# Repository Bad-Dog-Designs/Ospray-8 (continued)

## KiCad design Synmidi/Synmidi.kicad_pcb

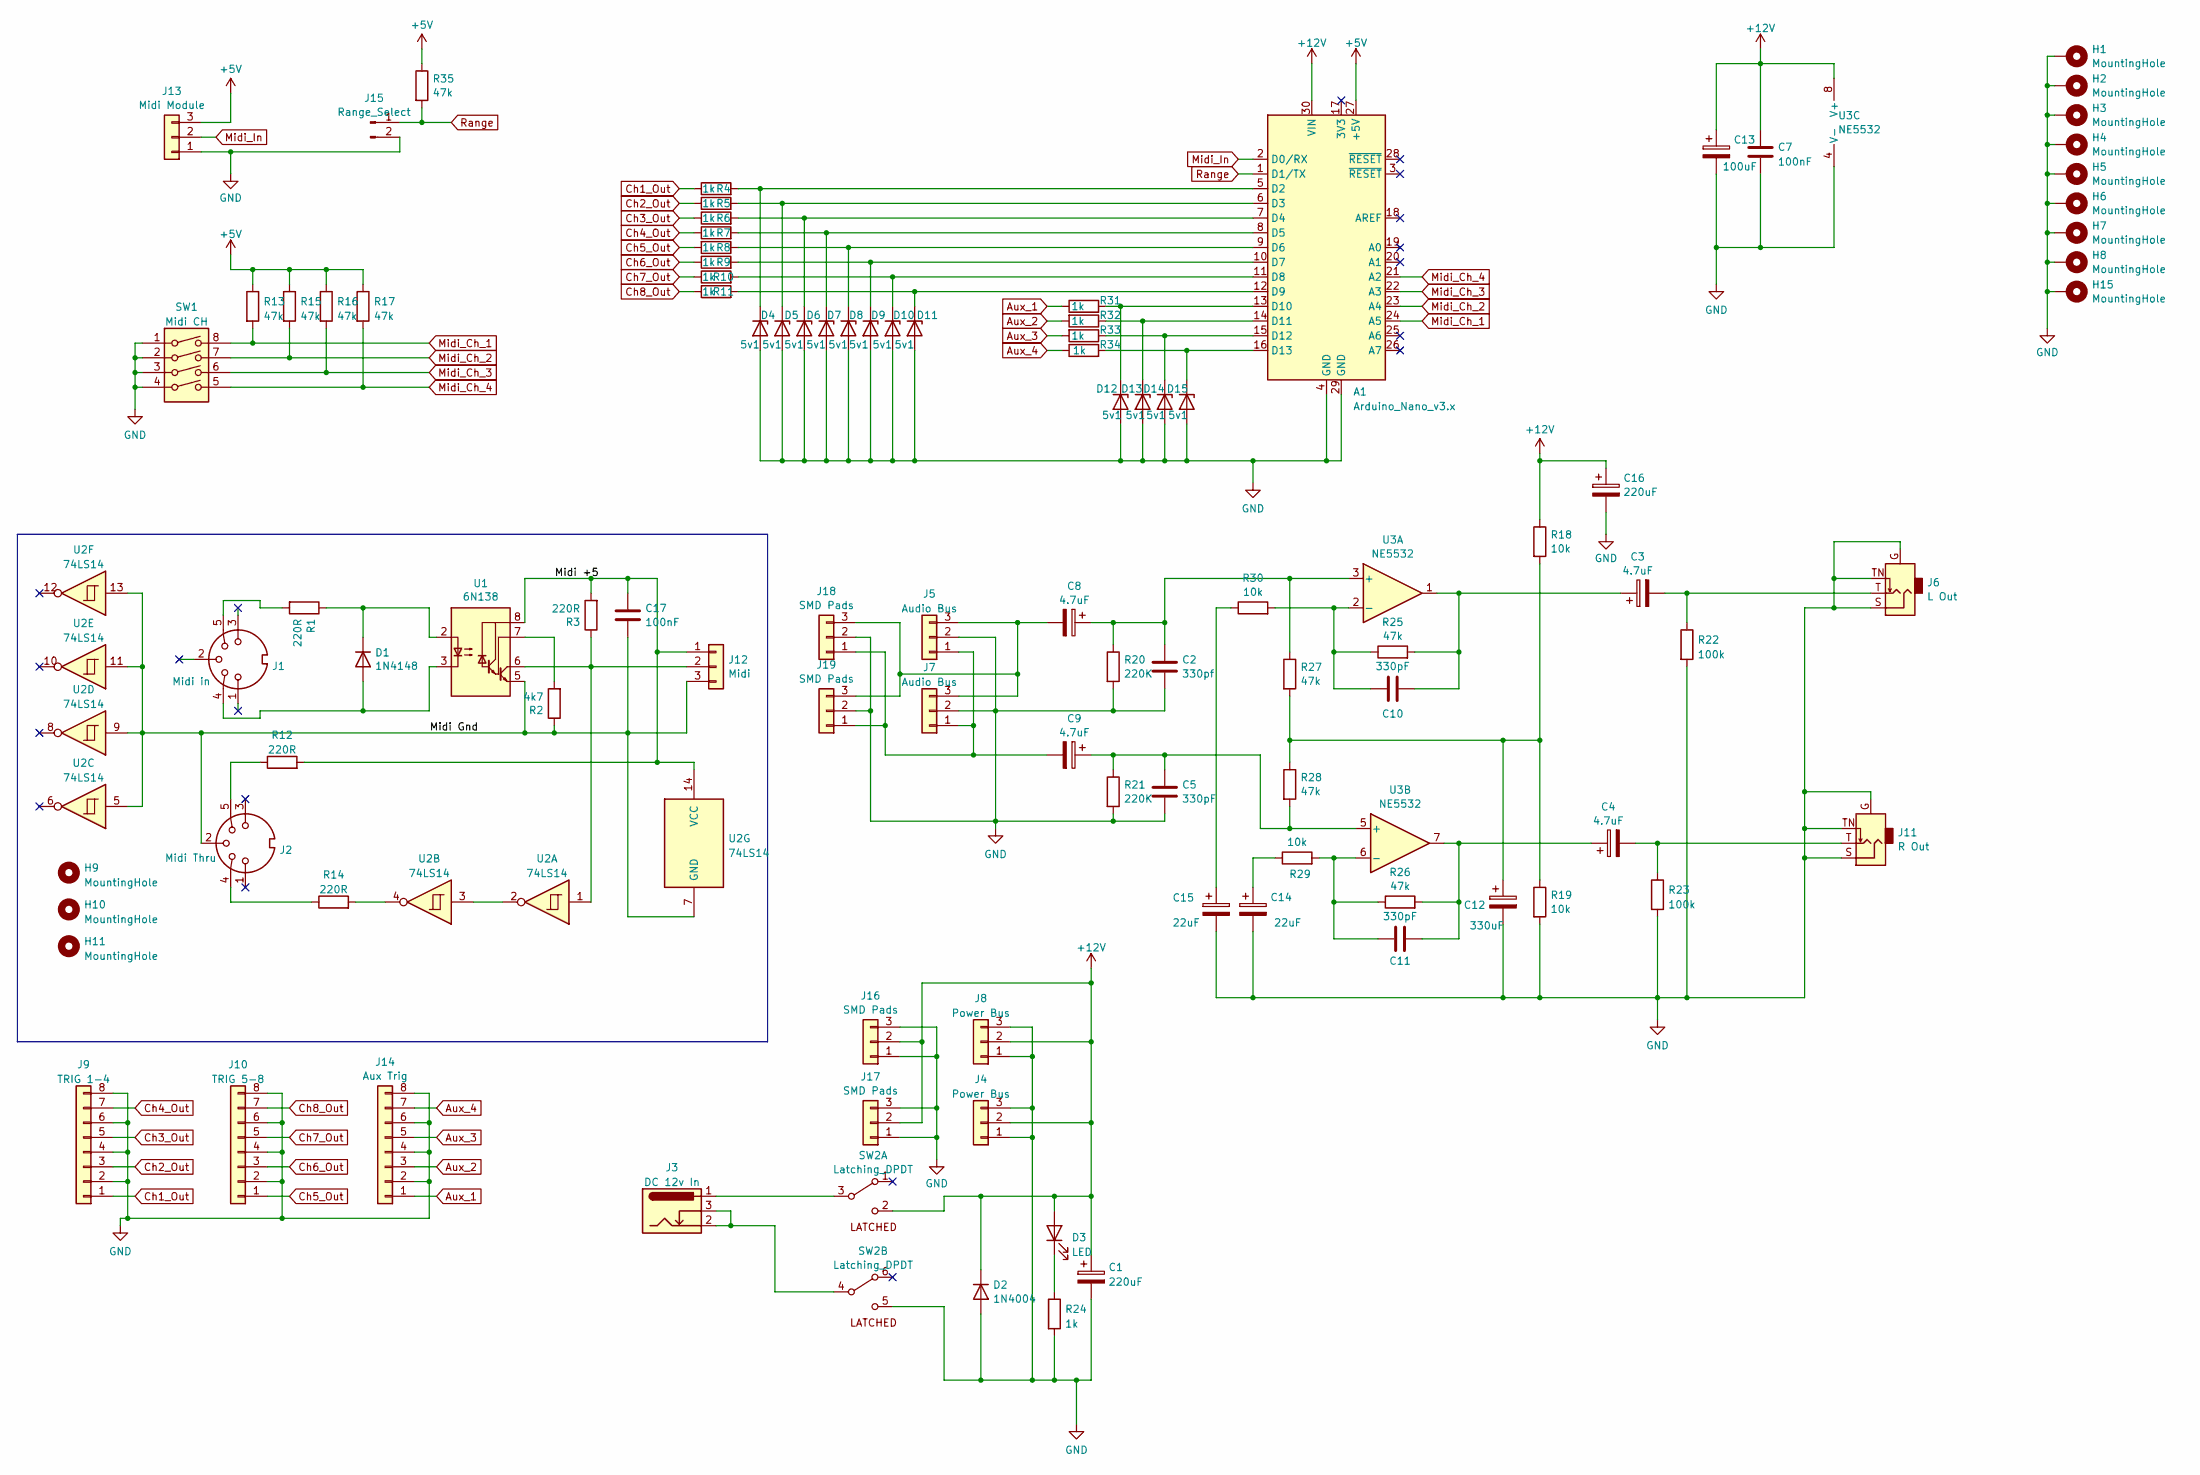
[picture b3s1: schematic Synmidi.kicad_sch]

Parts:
A1: Arduino_Nano_v3.x; Arduino_Nano
C1, C16: 220uF; CP_Radial_D10.0mm_P5.00mm
C2: 330pf; C_Disc_D4.3mm_W1.9mm_P5.00mm
C3, C4, C8, C9: 4.7uF; CP_Radial_D4.0mm_P1.50mm
C5, C10, C11: 330pF; C_Disc_D4.3mm_W1.9mm_P5.00mm
C7, C17: 100nF; C_0805_2012Metric
C12: 330uF; CP_Radial_D10.0mm_P5.00mm
C13: 100uF; CP_Radial_D8.0mm_P3.50mm
C14, C15: 22uF; CP_Radial_D5.0mm_P2.00mm
D1: 1N4148; D_MELF
D2: 1N4004; D_DO-41_SOD81_P10.16mm_Horizontal
D3: LED; LED_D3.0mm_FlatTop
D4, D5, D6, D7, D8, D9, D10, D11, D12, D13, D14, D15: 5v1; D_SOD-323
H1, H2, H3, H4, H5, H6, H7, H8, H9, H10, H11, H15: MountingHole; MountingHole_3.2mm_M3_DIN965_Pad
J1: Midi in; Midi_Socket
J2: Midi Thru; Midi_Socket
J3: DC 12v In; BarrelJack_GCT_DCJ200-10-A_Horizontal
J4, J8: Power Bus; PinHeader_1x03_P2.54mm_Horizontal
J5, J7: Audio Bus; PinHeader_1x03_P2.54mm_Horizontal
J6: L Out; 6.35mm_Socket_Mono
J9: TRIG 1-4; JST_EH_S8B-EH_1x08_P2.50mm_Horizontal
J10: TRIG 5-8; JST_EH_S8B-EH_1x08_P2.50mm_Horizontal
J11: R Out; 6.35mm_Socket_Mono
J12: Midi; PinHeader_1x03_P2.54mm_Vertical
J13: Midi Module; PinHeader_1x03_P2.54mm_Vertical
J14: Aux Trig; JST_EH_S8B-EH_1x08_P2.50mm_Horizontal
J15: Range_Select; PinHeader_1x02_P2.54mm_Vertical
J16, J17, J18, J19: SMD Pads; Bus Connector
R1, R3, R12, R14: 220R; R_1206_3216Metric
R2: 4k7; R_1206_3216Metric
R4, R5, R6, R7, R8, R9, R10, R11, R24, R31, R32, R33, R34: 1k; R_1206_3216Metric
R13, R15, R16, R17, R25, R26, R27, R28, R35: 47k; R_1206_3216Metric
R18, R19, R29, R30: 10k; R_1206_3216Metric
R20, R21: 220K; R_1206_3216Metric
R22, R23: 100k; R_1206_3216Metric
SW1: Midi CH; SW_DIP_SPSTx04_Piano_CTS_Series194-4MSTN_W7.62mm_P2.54mm
SW2: Latching_DPDT
U1: 6N138; DIP-8_W8.89mm_SMDSocket_LongPads
U2: 74LS14; SO-14_3.9x8.65mm_P1.27mm
U3: NE5532; SOIC-8_3.9x4.9mm_P1.27mm

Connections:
+5V: A1.27 (+5V), J13.3, R13.1, R15.1, R16.1, R17.1, R35.1
+12V: A1.30 (VIN), C1.1, C7.1, C13.1, C16.1, D2.1 (K), D3.2 (A), J4.2, J8.2, J16.2, J17.2, R18.1, SW2.2 (B), U3.8 (V+)
/Midi +5: C17.1, J12.1, R3.2, R12.2, U1.8 (VCC), U2.14 (VCC)
/Midi Gnd: C17.2, J2.2, J12.3, R2.1, U1.5 (GND), U2.5, U2.7 (GND), U2.9, U2.11, U2.13
Aux_1: J14.1, R31.1
Aux_2: J14.3, R32.2
Aux_3: J14.5, R33.2
Aux_4: J14.7, R34.1
Ch1_Out: J9.1, R4.1
Ch2_Out: J9.3, R5.1
Ch3_Out: J9.5, R6.1
Ch4_Out: J9.7, R7.1
Ch5_Out: J10.1, R8.2
Ch6_Out: J10.3, R9.1
Ch7_Out: J10.5, R10.1
Ch8_Out: J10.7, R11.1
GND: A1.4 (GND), A1.29 (GND), C1.2, C2.2, C5.2, C7.2, C12.2, C13.2, C14.2, C15.2, C16.2, D2.2 (A), D4.2 (A), D5.2 (A), D6.2 (A), D7.2 (A), D8.2 (A), D9.2 (A), D10.2 (A), D11.2 (A), D12.2 (A), D13.2 (A), D14.2 (A), D15.2 (A), H1.1, H2.1, H3.1, H4.1, H5.1, H6.1, H7.1, H8.1, H15.1, J4.1, J4.3, J5.2, J6.G, J6.S, J6.TN, J7.2, J8.1, J8.3, J9.2, J9.4, J9.6, J9.8, J10.2, J10.4, J10.6, J10.8, J11.G, J11.S, J11.TN, J13.1, J14.2, J14.4, J14.6, J14.8, J15.2, J16.1, J16.3, J17.1, J17.3, J18.2, J19.2, R19.2, R20.2, R21.2, R22.2, R23.2, R24.2, SW1.1, SW1.2, SW1.3, SW1.4, SW2.5 (B), U3.4 (V-)
Midi_Ch_1: A1.24 (A5), R13.2, SW1.8
Midi_Ch_2: A1.23 (A4), R15.2, SW1.7
Midi_Ch_3: A1.22 (A3), R16.2, SW1.6
Midi_Ch_4: A1.21 (A2), R17.2, SW1.5
Midi_In: A1.2 (D0/RX), J13.2
unnamed: A1.5 (D2), D4.1 (K), R4.2
unnamed: A1.6 (D3), D5.1 (K), R5.2
unnamed: A1.7 (D4), D6.1 (K), R6.2
unnamed: A1.8 (D5), D7.1 (K), R7.2
unnamed: A1.9 (D6), D8.1 (K), R8.1
unnamed: A1.10 (D7), D9.1 (K), R9.2
unnamed: A1.11 (D8), D10.1 (K), R10.2
unnamed: A1.12 (D9), D11.1 (K), R11.2
unnamed: A1.13 (D10), D12.1 (K), R31.2
unnamed: A1.14 (D11), D13.1 (K), R32.1
unnamed: A1.15 (D12), D14.1 (K), R33.1
unnamed: A1.16 (D13), D15.1 (K), R34.2
unnamed: C3.2, J6.T, R22.1
unnamed: C4.2, J11.T, R23.1
unnamed: C3.1, C10.2, R25.2, U3.1
unnamed: C4.1, C11.2, R26.2, U3.7
unnamed: C12.1, R18.2, R19.1, R27.2, R28.1
unnamed: C14.1, R29.1
unnamed: C15.1, R30.1
unnamed: D1.2 (A), J1.4, U1.3 (C2)
unnamed: D1.1 (K), R1.1, U1.2 (C1)
unnamed: D3.1 (K), R24.1
unnamed: J1.5, R1.2
unnamed: J2.4, R14.1
unnamed: J2.5, R12.1
unnamed: J12.2, R3.1, U1.6 (VO2), U2.1
unnamed: C9.2, J5.1, J7.1, J18.1, J19.1
unnamed: C8.2, J5.3, J7.3, J18.3, J19.3
unnamed: R14.2, U2.4
unnamed: J3.1, SW2.3 (C)
unnamed: J3.2, J3.3, SW2.4 (A)
unnamed: R2.2, U1.7 (VO1)
unnamed: U2.2, U2.3
unnamed: C2.1, C8.1, R20.1, R27.1, U3.3 (+)
unnamed: C10.1, R25.1, R30.2, U3.2 (-)
unnamed: C5.1, C9.1, R21.1, R28.2, U3.5 (+)
unnamed: C11.1, R26.1, R29.2, U3.6 (-)
Range: A1.1 (D1/TX), J15.1, R35.2

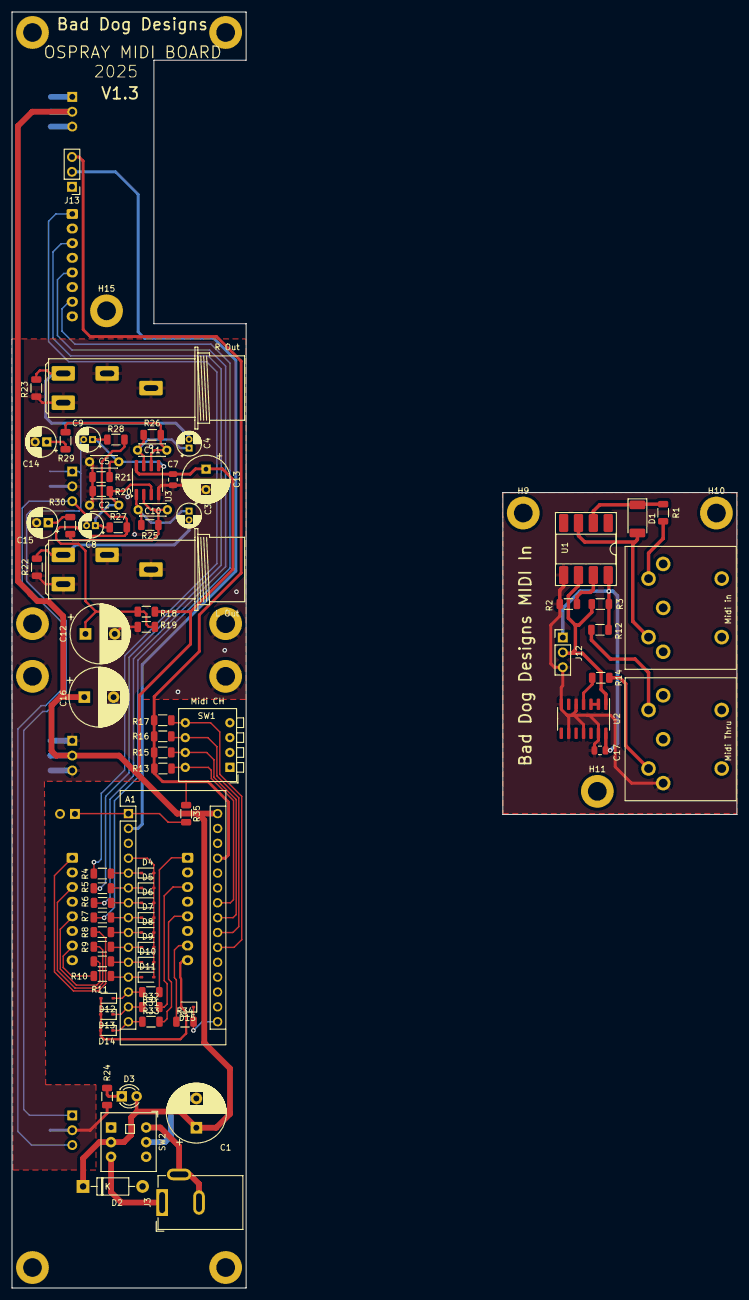
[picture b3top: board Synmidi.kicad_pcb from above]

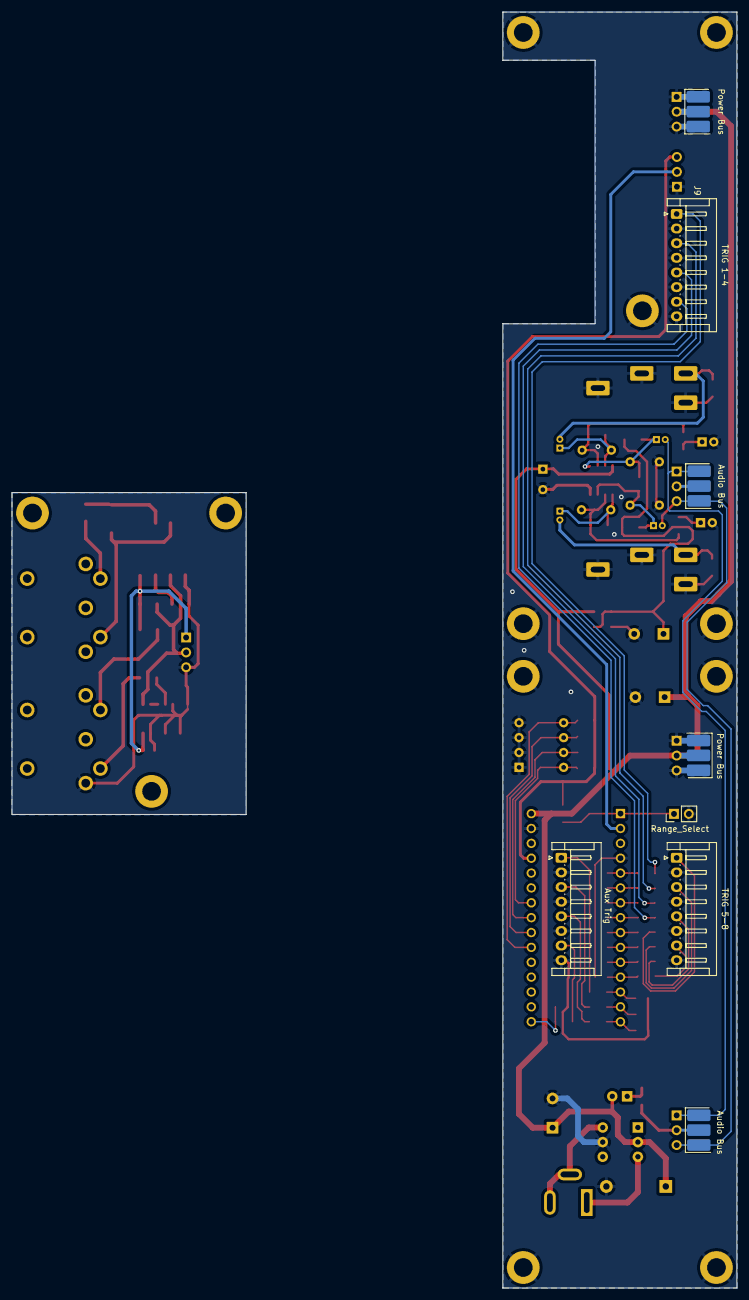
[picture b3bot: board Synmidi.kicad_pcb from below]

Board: 2 copper layers, 123.8 x 218.0 mm, 103 parts (12 on the bottom side), 60 nets.

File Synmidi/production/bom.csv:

Designator,Footprint,Quantity,Value,LCSC Part #
A1,Arduino_Nano,1,Arduino_Nano_v3.x,
"C1, C16",CP_Radial_D10.0mm_P5.00mm,2,220uF,
"C10, C11, C2, C5",C_Disc_D4.3mm_W1.9mm_P5.00mm,4,330pF,
C12,CP_Radial_D10.0mm_P5.00mm,1,330uF,
C13,CP_Radial_D8.0mm_P3.50mm,1,100uF,
"C14, C15",CP_Radial_D5.0mm_P2.00mm,2,22uF,
"C17, C7",0805,2,100nF,
"C3, C4, C8, C9",CP_Radial_D4.0mm_P1.50mm,4,4.7uF,
D1,D_MELF,1,1N4148,
"D10, D11, D12, D13, D14, D15, D4, D5, D6, D7, D8, D9",D_SOD-323,12,5v1,
D2,D_DO-41_SOD81_P10.16mm_Horizontal,1,1N4004,
D3,LED_D3.0mm_FlatTop,1,LED,
"H10, H11, H9",MountingHole_3.2mm_M3_DIN965_Pad,3,MountingHole,
J1,Midi_Socket,1,Midi in,
J10,JST_EH_S8B-EH_1x08_P2.50mm_Horizontal,1,TRIG 5-8,
J11,6.35mm_Socket_Mono,1,R Out,
J12,PinHeader_1x03_P2.54mm_Vertical,1,Midi,
J13,PinHeader_1x03_P2.54mm_Vertical,1,Midi Module,
J14,JST_EH_S8B-EH_1x08_P2.50mm_Horizontal,1,Aux Trig,
J15,PinHeader_1x02_P2.54mm_Vertical,1,Range_Select,
"J16, J17, J18, J19",Bus Connector,4,SMD Pads,
J2,Midi_Socket,1,Midi Thru,
J3,BarrelJack_GCT_DCJ200-10-A_Horizontal,1,DC 12v In,
"J4, J8",PinHeader_1x03_P2.54mm_Horizontal,2,Power Bus,
"J5, J7",PinHeader_1x03_P2.54mm_Horizontal,2,Audio Bus,
J6,6.35mm_Socket_Mono,1,L Out,
J9,JST_EH_S8B-EH_1x08_P2.50mm_Horizontal,1,TRIG 1-4,
"R1, R12, R14, R3",1206,4,220R,
"R10, R11, R24, R31, R32, R33, R34, R4, R5, R6, R7, R8, R9",1206,13,1k,
"R13, R15, R16, R17, R25, R26, R27, R28, R35",1206,9,47k,
"R18, R19, R29, R30",1206,4,10k,
R2,1206,1,4k7,
"R20, R21",1206,2,220K,
"R22, R23",1206,2,100k,
SW1,SW_DIP_SPSTx04_Piano_CTS_Series194-4MSTN_W7.62mm_P2.54mm,1,Midi CH,
SW2,Latching_DPDT,1,Latching_DPDT,
U1,DIP-8_W8.89mm_SMDSocket_LongPads,1,6N138,
U2,SO-14_3.9x8.65mm_P1.27mm,1,74LS14,
U3,SOIC-8_3.9x4.9mm_P1.27mm,1,NE5532,

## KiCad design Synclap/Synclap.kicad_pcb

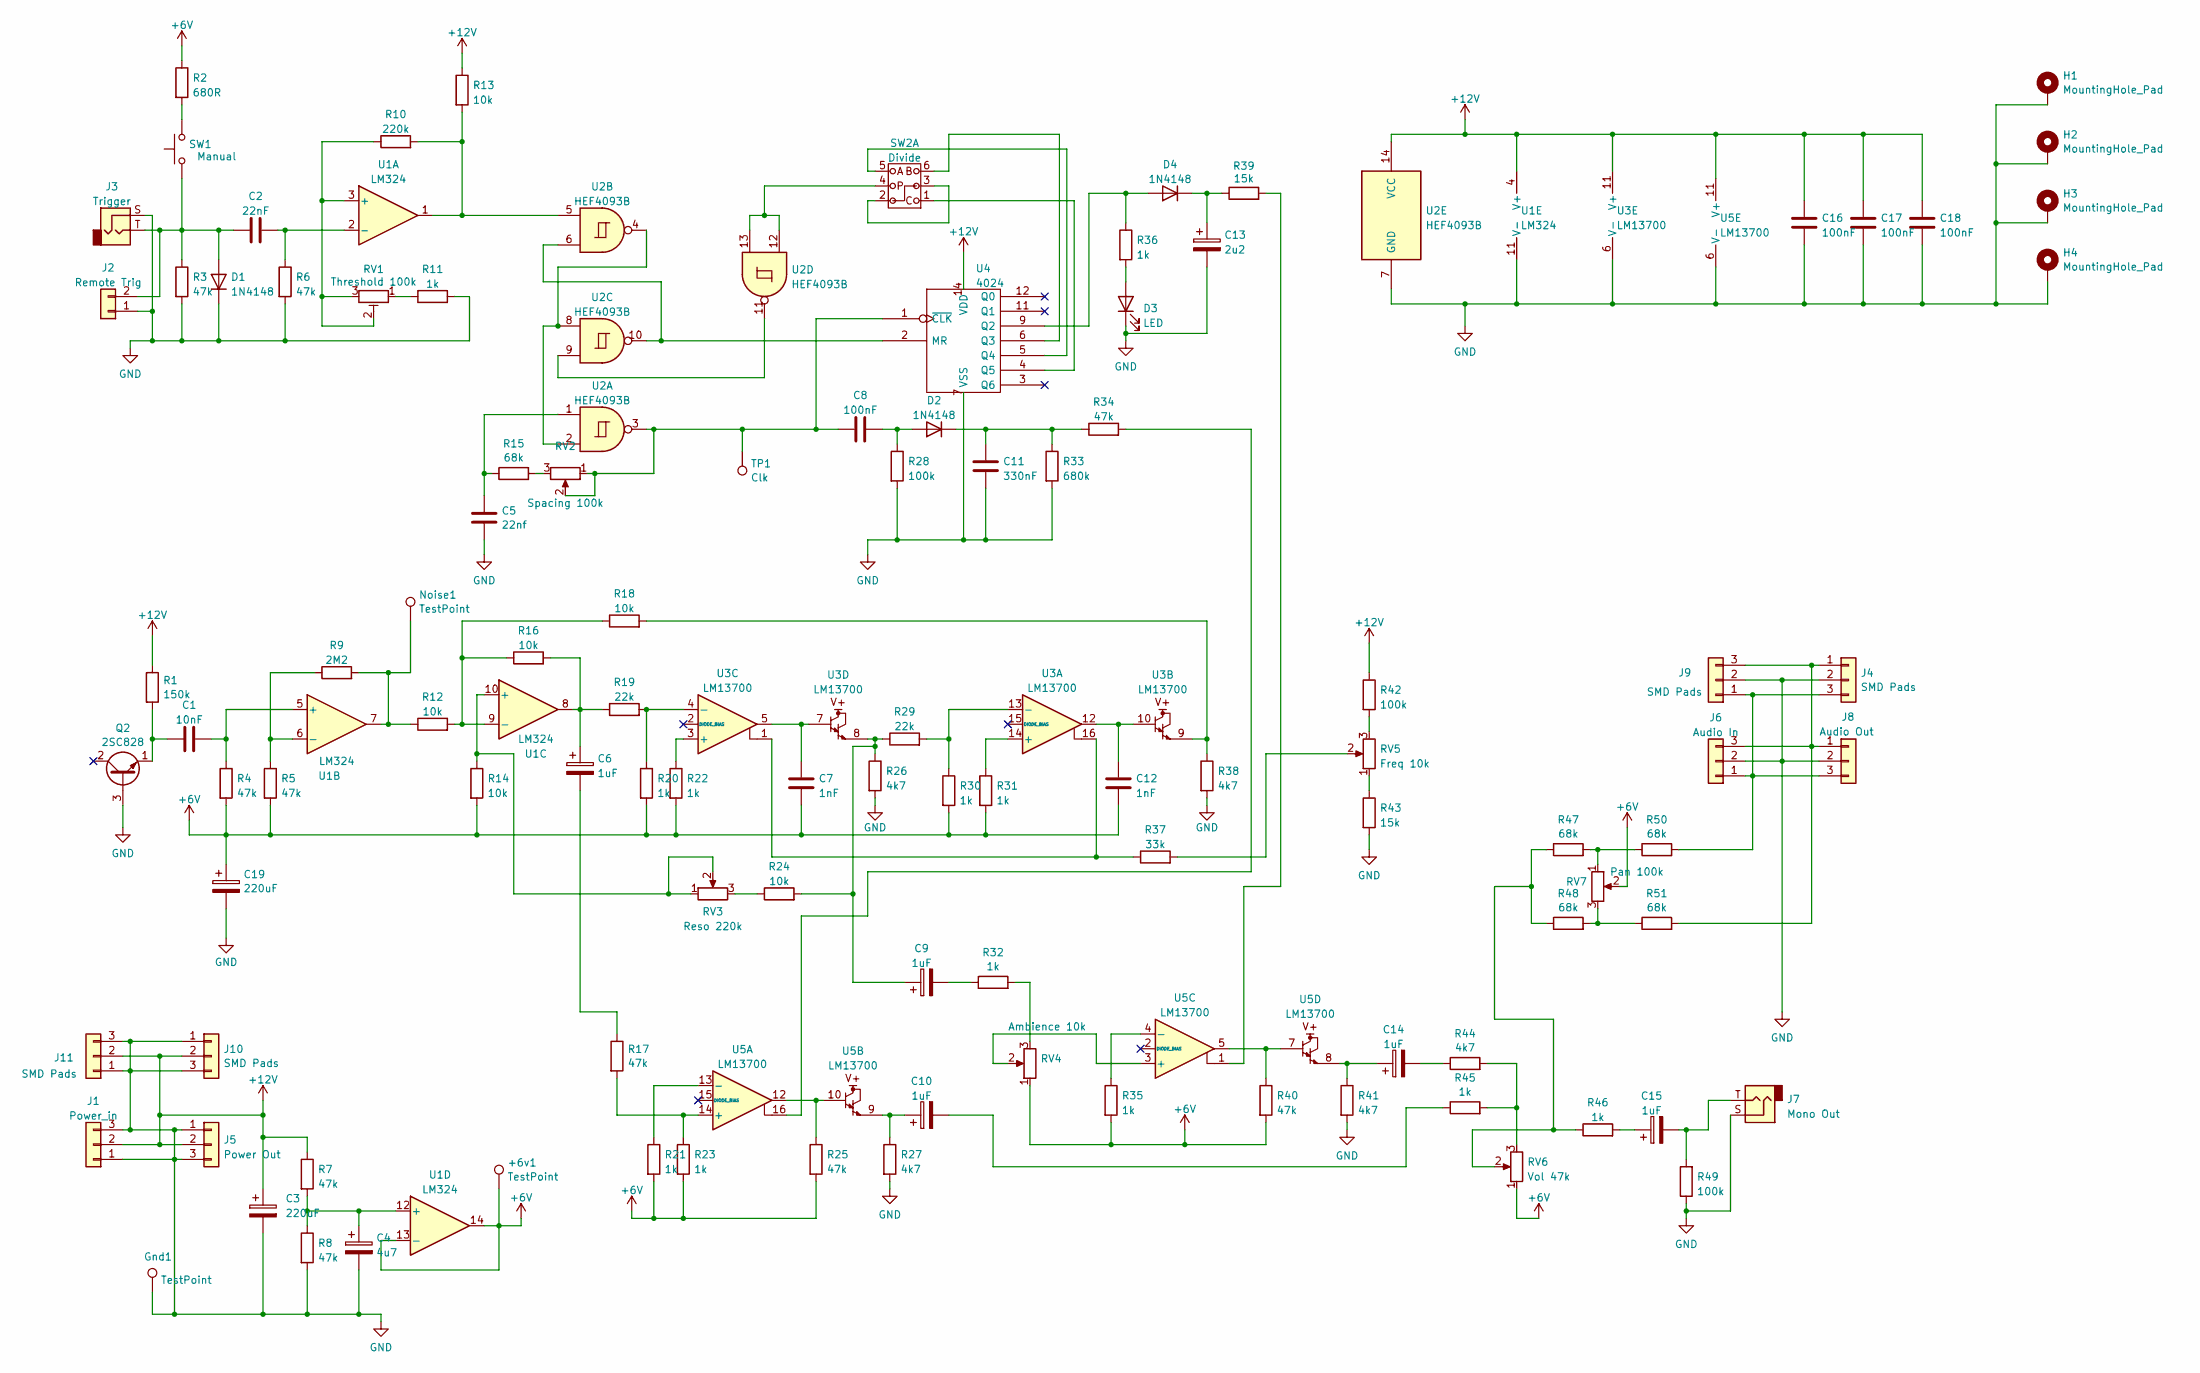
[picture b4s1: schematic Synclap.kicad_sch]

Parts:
+6v1: TestPoint; TestPoint_THTPad_D1.5mm_Drill0.7mm
C1: 10nF; C_Disc_D4.3mm_W1.9mm_P5.00mm
C2: 22nF; C_Disc_D4.3mm_W1.9mm_P5.00mm
C3: 220uF; CP_Radial_D8.0mm_P3.50mm
C4: 4u7; CP_Radial_D4.0mm_P1.50mm
C5: 22nf; C_Disc_D4.3mm_W1.9mm_P5.00mm
C6, C9, C10, C14, C15: 1uF; CP_Radial_D4.0mm_P1.50mm
C7, C12: 1nF; C_Disc_D4.3mm_W1.9mm_P5.00mm
C8: 100nF; C_Disc_D4.3mm_W1.9mm_P5.00mm
C11: 330nF; C_Disc_D4.7mm_W2.5mm_P5.00mm
C13: 2u2; CP_Radial_D4.0mm_P1.50mm
C16, C17, C18: 100nF; C_0805_2012Metric
C19: 220uF; CP_Radial_D6.3mm_P2.50mm
D1, D2, D4: 1N4148; D_MiniMELF
D3: LED; LED_D3.0mm
Gnd1: TestPoint; TestPoint_THTPad_D1.5mm_Drill0.7mm
H1, H2, H3, H4: MountingHole_Pad; MountingHole_3.2mm_M3_DIN965_Pad
J1: Power_in; PinHeader_1x03_P2.54mm_Horizontal
J2: Remote Trig; PinHeader_1x02_P2.54mm_Vertical
J3: Trigger; Jack_3.5mm_QingPu_WQP-PJ398SM_Vertical_CircularHoles
J4, J9, J10, J11: SMD Pads; Bus Connector
J5: Power Out; PinHeader_1x03_P2.54mm_Horizontal
J6: Audio In; PinHeader_1x03_P2.54mm_Horizontal
J7: Mono Out; Jack_3.5mm_QingPu_WQP-PJ398SM_Vertical_CircularHoles
J8: Audio Out; PinHeader_1x03_P2.54mm_Horizontal
Noise1: TestPoint; TestPoint_THTPad_D1.5mm_Drill0.7mm
Q2: 2SC828; TO-92_Inline
R1: 150k; R_1206_3216Metric
R2: 680R; R_1206_3216Metric
R3, R4, R5, R6, R7, R8, R17, R25, R34, R40: 47k; R_1206_3216Metric
R9: 2M2; R_1206_3216Metric
R10: 220k; R_1206_3216Metric
R11, R20, R21, R22, R23, R30, R31, R32, R35, R36, R45, R46: 1k; R_1206_3216Metric
R12, R13, R14, R16, R18, R24: 10k; R_1206_3216Metric
R15, R47, R48, R50, R51: 68k; R_1206_3216Metric
R19, R29: 22k; R_1206_3216Metric
R26, R27, R38, R41, R44: 4k7; R_1206_3216Metric
R28, R42, R49: 100k; R_1206_3216Metric
R33: 680k; R_1206_3216Metric
R37: 33k; R_1206_3216Metric
R39, R43: 15k; R_1206_3216Metric
RV1: Threshold 100k; Potentiometer_Piher_PT-6-V_Vertical
RV2: Spacing 100k; Potentiometer_Alps_RK09K_Single_Vertical
RV3: Reso 220k; Potentiometer_Alps_RK09K_Single_Vertical
RV4: Ambience 10k; Potentiometer_Alps_RK09K_Single_Vertical
RV5: Freq 10k; Potentiometer_Alps_RK09K_Single_Vertical
RV6: Vol 47k; Potentiometer_Alps_RK09K_Single_Vertical
RV7: Pan 100k; Potentiometer_Alps_RK09K_Single_Vertical
SW1: Manual; SW_PUSH_6mm
SW2: Divide; 1P3WSW
TP1: Clk; TestPoint_THTPad_D1.5mm_Drill0.7mm
U1: LM324; SO-14_3.9x8.65mm_P1.27mm
U2: HEF4093B; SO-14_3.9x8.65mm_P1.27mm
U3, U5: LM13700; SO-16_3.9x9.9mm_P1.27mm
U4: 4024; SO-14_3.9x8.65mm_P1.27mm

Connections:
+6V: +6v1.1, C7.2, C12.2, C19.1, R2.1, R4.2, R5.2, R14.2, R20.2, R21.2, R22.2, R23.2, R25.2, R30.2, R31.2, R35.2, R40.2, RV4.1, RV6.1, RV7.2, U1.13 (-), U1.14; also elsewhere on the board
+12V: C3.1, C16.1, C17.1, C18.1, J1.2, J5.2, J10.2, J11.2, R1.1, R7.1, R13.1, R42.1, U1.4 (V+), U2.14 (VCC), U3.11 (V+), U4.14 (VDD), U5.11 (V+)
GND: C3.2, C4.2, C5.2, C11.2, C13.2, C16.2, C17.2, C18.2, C19.2, D1.1 (K), D3.1 (K), Gnd1.1, H1.1, H2.1, H3.1, H4.1, J1.1, J1.3, J2.1, J3.S, J4.2, J5.1, J5.3, J6.2, J7.S, J8.2, J9.2, J10.1, J10.3, J11.1, J11.3, Q2.3 (B), R3.2, R6.2, R8.2, R11.2, R26.2, R27.2, R28.2, R33.2, R38.2, R41.2, R43.2, R49.1, RV2.MP, RV3.MP, RV4.MP, RV5.MP, RV6.MP, RV7.MP, U1.11 (V-), U2.7 (GND), U3.6 (V-), U4.7 (VSS), U5.6 (V-); also elsewhere on the board
unnamed: C5.1, R15.1, U2.1
unnamed: C6.1, R16.2, R19.1, U1.8
unnamed: C6.2, R17.1
unnamed: C7.1, U3.5, U3.7
unnamed: C9.1, R24.2, R26.1, R29.1, U3.8
unnamed: C9.2, R32.1
unnamed: C10.1, R27.1, U5.9
unnamed: C10.2, R45.1
unnamed: C12.1, U3.10, U3.12
unnamed: C14.1, R41.1, U5.8
unnamed: C14.2, R44.1
unnamed: C15.1, R46.2
unnamed: C15.2, J7.T, R49.2
unnamed: C2.1, D1.2 (A), J2.2, J3.T, R3.1, SW1.1
unnamed: C8.2, D2.2 (A), R28.1
unnamed: C11.1, D2.1 (K), R33.1, R34.1
unnamed: D3.2 (A), R36.2
unnamed: D4.2 (A), R36.1, U4.9 (Q2)
unnamed: C13.1, D4.1 (K), R39.1
unnamed: J4.1, J6.3, J8.1, J9.3, R51.2
unnamed: J4.3, J6.1, J8.3, J9.1, R50.2
unnamed 24: Noise1.1, R9.2, R12.1, U1.7; also elsewhere on the board
unnamed: C1.1, Q2.1 (E), R1.2
unnamed: R2.2, SW1.2
unnamed: R10.2, R13.2, U1.1, U2.5
unnamed: R11.1, RV1.1
unnamed: R15.2, RV2.3
unnamed: R18.2, R38.1, U3.9
unnamed: R24.1, RV3.3
unnamed: R25.1, U5.10, U5.12
unnamed: R32.2, RV4.3
unnamed: R34.2, U5.16
unnamed: R37.1, U3.1, U3.16
unnamed: R37.2, RV5.2
unnamed: R39.2, U5.1
unnamed: R40.1, U5.5, U5.7
unnamed: R42.2, RV5.3
unnamed: R43.1, RV5.1
unnamed: R44.2, R45.2, RV6.3
unnamed: R46.1, R47.1, R48.1, RV6.2
unnamed: R47.2, R50.1, RV7.1
unnamed: R48.2, R51.1, RV7.3
unnamed: SW2.2, SW2.3
unnamed: SW2.4, U2.12, U2.13
unnamed: R10.1, RV1.2, RV1.3, U1.3 (+)
unnamed: C2.2, R6.1, U1.2 (-)
unnamed: C1.2, R4.1, U1.5 (+)
unnamed: R5.1, R9.1, U1.6 (-)
unnamed: R14.1, RV3.1, RV3.2, U1.10 (+)
unnamed: R12.2, R16.1, R18.1, U1.9 (-)
unnamed: C4.1, R7.2, R8.1, U1.12 (+)
unnamed: U2.2, U2.4, U2.8
unnamed: U2.9, U2.11
unnamed: R31.1, U3.14 (+)
unnamed: R29.2, R30.1, U3.13 (-)
unnamed: R22.1, U3.3 (+)
unnamed: R19.2, R20.1, U3.4 (-)
unnamed: U2.6, U2.10, U4.2 (MR)
unnamed: SW2.6, U4.6 (Q3)
unnamed: SW2.5, U4.5 (Q4)
unnamed: SW2.1, U4.4 (Q5)
unnamed 64: C8.1, RV2.1, RV2.2, TP1.1, U2.3, U4.1 (~CLK); also elsewhere on the board
unnamed: R17.2, R23.1, U5.14 (+)
unnamed: R21.1, U5.13 (-)
unnamed: RV4.2, U5.3 (+)
unnamed: R35.1, U5.4 (-)

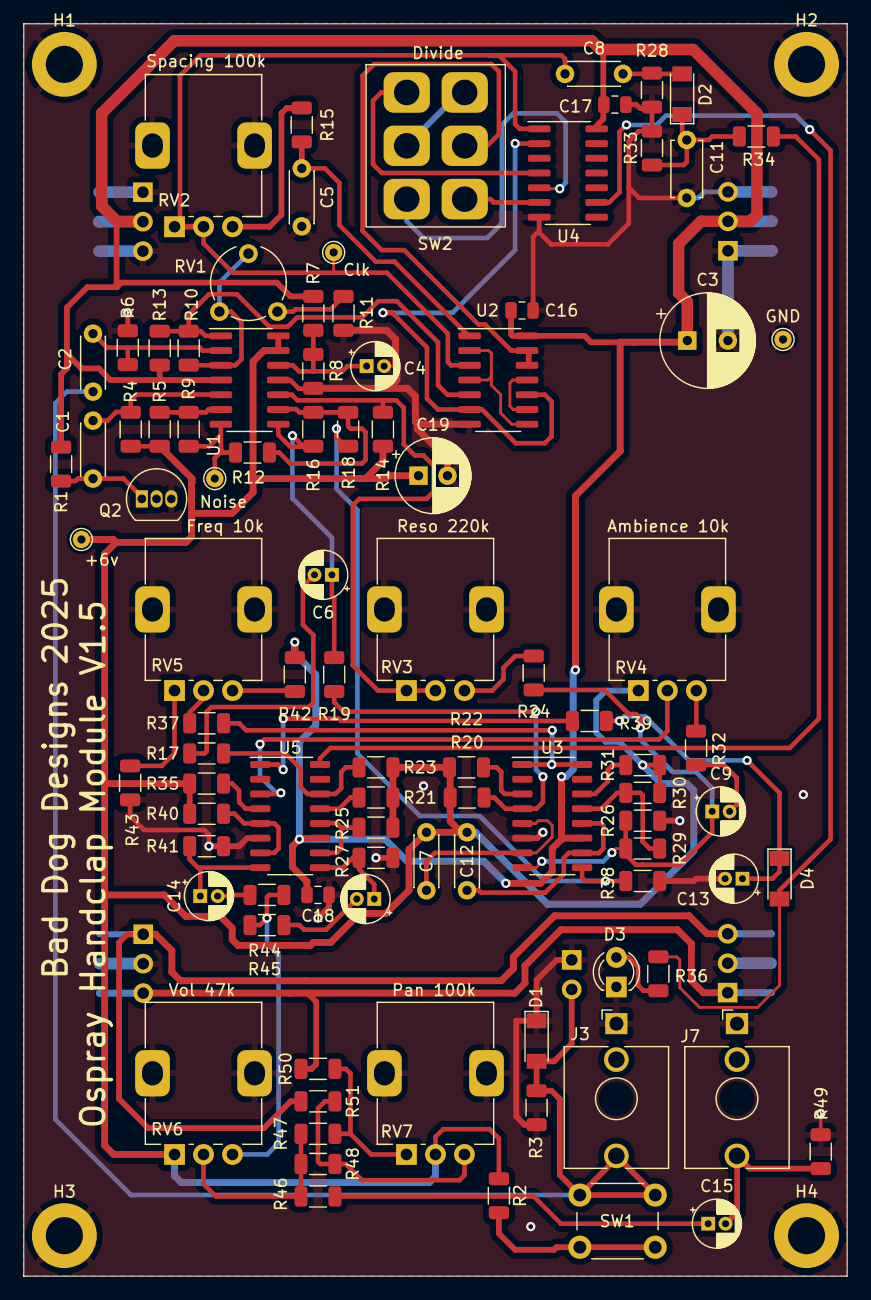
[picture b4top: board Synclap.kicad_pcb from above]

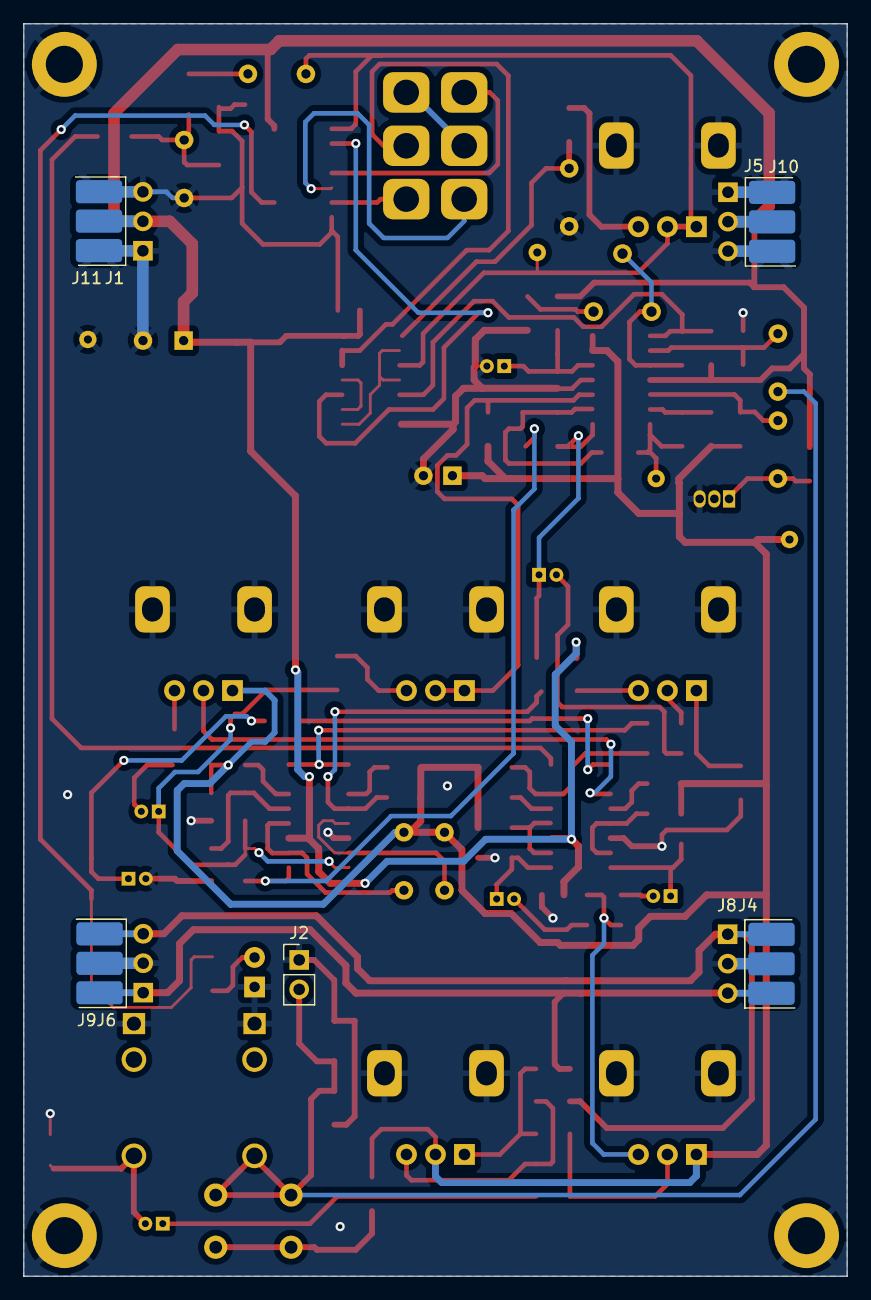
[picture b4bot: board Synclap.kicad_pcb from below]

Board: 2 copper layers, 71.0 x 108.0 mm, 108 parts (9 on the bottom side), 69 nets.

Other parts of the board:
+6v: TestPoint; TestPoint_THTPad_D1.5mm_Drill0.7mm
Clk: Clk; TestPoint_THTPad_D1.5mm_Drill0.7mm
GND: TestPoint; TestPoint_THTPad_D1.5mm_Drill0.7mm
Noise: TestPoint; TestPoint_THTPad_D1.5mm_Drill0.7mm

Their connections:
+6V: +6v.1; also elsewhere on the board
GND: GND.1; also elsewhere on the board
unnamed 24: Noise.1; also elsewhere on the board
unnamed 64: Clk.1; also elsewhere on the board

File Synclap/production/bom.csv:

Designator,Footprint,Quantity,Value,LCSC Part #
"+6V, GND, NOISE",TestPoint_THTPad_D1.5mm_Drill0.7mm,3,TestPoint,
C1,C_Disc_D4.3mm_W1.9mm_P5.00mm,1,10nF,
"C10, C14, C15, C6, C9",CP_Radial_D4.0mm_P1.50mm,5,1uF,
C11,C_Disc_D4.7mm_W2.5mm_P5.00mm,1,330nF,
"C12, C7",C_Disc_D4.3mm_W1.9mm_P5.00mm,2,1nF,
C13,CP_Radial_D4.0mm_P1.50mm,1,2u2,
"C16, C17, C18",0805,3,100nF,
C19,CP_Radial_D6.3mm_P2.50mm,1,220uF,
"C2, C5",C_Disc_D4.3mm_W1.9mm_P5.00mm,2,22nF,
C3,CP_Radial_D8.0mm_P3.50mm,1,220uF,
C4,CP_Radial_D4.0mm_P1.50mm,1,4u7,
C8,C_Disc_D4.3mm_W1.9mm_P5.00mm,1,100nF,
CLK,TestPoint_THTPad_D1.5mm_Drill0.7mm,1,Clk,
"D1, D2, D4",D_MiniMELF,3,1N4148,
D3,LED_D3.0mm,1,LED,
J1,PinHeader_1x03_P2.54mm_Horizontal,1,Power_in,
"J10, J11, J4, J9",Bus Connector,4,SMD Pads,
J2,PinHeader_1x02_P2.54mm_Vertical,1,Remote Trig,
J3,Jack_3.5mm_QingPu_WQP-PJ398SM_Vertical_CircularHoles,1,Trigger,
J5,PinHeader_1x03_P2.54mm_Horizontal,1,Power Out,
J6,PinHeader_1x03_P2.54mm_Horizontal,1,Audio In,
J7,Jack_3.5mm_QingPu_WQP-PJ398SM_Vertical_CircularHoles,1,Mono Out,
J8,PinHeader_1x03_P2.54mm_Horizontal,1,Audio Out,
Q2,TO-92_Inline,1,2SC828,
R1,1206,1,150k,
R10,1206,1,220k,
"R11, R20, R21, R22, R23, R30, R31, R32, R35, R36, R45, R46",1206,12,1k,
"R12, R13, R14, R16, R18, R24",1206,6,10k,
"R15, R47, R48, R50, R51",1206,5,68k,
"R17, R25, R3, R34, R4, R40, R5, R6, R7, R8",1206,10,47k,
"R19, R29",1206,2,22k,
R2,1206,1,680R,
"R26, R27, R38, R41, R44",1206,5,4k7,
"R28, R42, R49",1206,3,100k,
R33,1206,1,680k,
R37,1206,1,33k,
"R39, R43",1206,2,15k,
R9,1206,1,2M2,
RV1,Potentiometer_Piher_PT-6-V_Vertical,1,Threshold 100k,
RV2,Potentiometer_Alps_RK09K_Single_Vertical,1,Spacing 100k,
RV3,Potentiometer_Alps_RK09K_Single_Vertical,1,Reso 220k,
RV4,Potentiometer_Alps_RK09K_Single_Vertical,1,Ambience 10k,
RV5,Potentiometer_Alps_RK09K_Single_Vertical,1,Freq 10k,
RV6,Potentiometer_Alps_RK09K_Single_Vertical,1,Vol 47k,
RV7,Potentiometer_Alps_RK09K_Single_Vertical,1,Pan 100k,
SW1,SW_PUSH_6mm,1,Manual,
SW2,1P3WSW,1,Divide,
U1,SO-14_3.9x8.65mm_P1.27mm,1,LM324,
U2,SO-14_3.9x8.65mm_P1.27mm,1,HEF4093B,
"U3, U5",SO-16_3.9x9.9mm_P1.27mm,2,LM13700,
U4,SO-14_3.9x8.65mm_P1.27mm,1,4024,

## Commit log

2026-06-27 Front Panel and side panel artwork
2026-06-27 Arduino Code for Midi input
2026-06-27 Synclap KiCad project files and production files
2026-06-27 Midi interface / Line output Amp KiCad Project
2026-06-27 Syntom KiCad project files
2026-06-27 Synbal KiCad Project files
